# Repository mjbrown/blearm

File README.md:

# blearm
Open source hardware, firmware, and software for a Bluetooth Low Energy PiHAT.  This PiHAT was used to control a robot arm demonstration for Maker Faire MSP.

1. Firmware includes BGScript and XML files which define the embedded Bluetooth Low Energy device.  
2. Mechanical files include all 3d printed models used to construct the robot arm.  
3. Hardware files include schematics and layout eagle files for the circuit board.  
4. Software includes python scripts used in the development of the hardware.xml settings for PWM.
5. Android includes the modified Bluetooth LE Android application used to control the blearm.

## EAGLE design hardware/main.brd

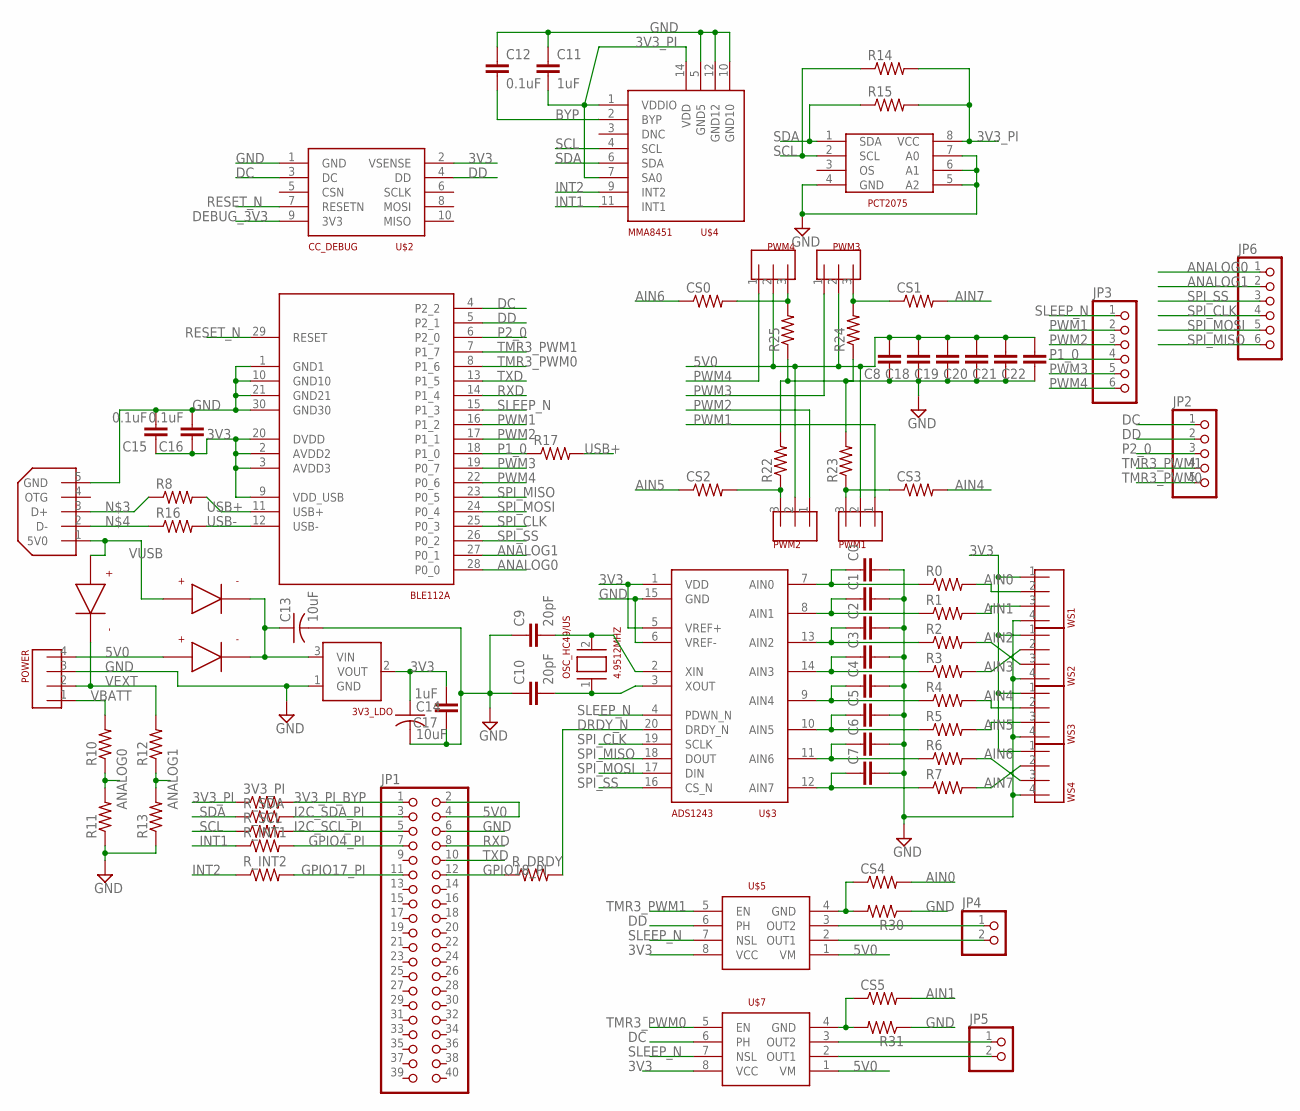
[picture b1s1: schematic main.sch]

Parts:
3V3_LDO: MCP1700; SOT23
3V3_PI: R-US_R0603; R0603
4.9512MHZ: OSC_HC49/US; HC49UP
BLE112A: BLE112A; BLE112
C0, C1, C2, C3, C4, C5, C6, C7, C8, C18, C19, C20, C21, C22: C-EUC0603; C0603
C9, C10: 20pF; C0603
C11, C17: 1uF; C0603
C12, C15, C16: 0.1uF; C0603
C13, C14: 10uF; C0805
CS0, CS1, CS2, CS3, CS4, CS5: R-US_R0603; R0603
JP1: PINHD-2X20; 2X20
JP2: PINHD-1X5; 1X05
JP3, JP6: PINHD-1X6; 1X06
JP4, JP5: PINHD-1X2; 1X02
PCT2075: PCT2075; SO-08
POWER: HDR_SPOX4
PWM1, PWM2, PWM3, PWM4: HDR_1X3
R0, R1, R2, R3, R4, R5, R6, R7, R8, R10, R11, R12, R13, R14, R15, R16, R17: R-US_R0603; R0603
R22, R23, R24, R25, R30, R31: R-US_R1206; R1206
R_DRDY: R-US_R0603; R0603
R_INT1, R_INT2: R-US_R0603; R0603
R_SCL: R-US_R0603; R0603
R_SDA: R-US_R0603; R0603
U$1, U$11, U$12: SCHOTTKEY_DIODE_1206; DIODE_1206
U$2: CC_DEBUG; HDR_2X5_127MM
U$3: ADS1243; TSSOP20
U$4: MMA8451; QFN16_3X3
U$5, U$7: DRV8838; WSON-8-PAD
U$6: MICRO_USB
WS1, WS2, WS3, WS4: HDR_1X4

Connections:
3V3: 3V3_LDO.2 (VOUT), BLE112A.2 (AVDD2), BLE112A.3 (AVDD3), BLE112A.9 (VDD_USB), BLE112A.20 (DVDD), C14.1, C15.1, C16.1, C17.2, U$2.2 (VSENSE), U$3.1 (VDD), U$3.5 (VREF+), U$5.8 (VCC), U$7.8 (VCC), WS1.1, WS2.1, WS3.1, WS4.1
3V3_PI: 3V3_PI.1, C11.2, PCT2075.8 (VCC), R14.2, R15.2, U$4.1 (VDDIO), U$4.7 (SA0), U$4.14 (VDD)
3V3_PI_BYP: 3V3_PI.2, JP1.1
5V0: C8.2, C18.2, C19.2, C20.2, C21.2, C22.2, JP1.2, JP1.4, POWER.4, PWM1.2, PWM2.2, PWM3.2, PWM4.2, U$5.1 (VM), U$7.1 (VM), U$12.CATHODE+
AIN0: CS4.2, R0.2, WS1.2
AIN1: CS5.2, R1.2, WS1.3
AIN2: R2.2, WS2.3
AIN3: R3.2, WS2.2
AIN4: CS3.2, R4.2, WS3.2
AIN5: CS2.1, R5.2, WS3.3
AIN6: CS0.1, R6.2, WS4.3
AIN7: CS1.2, R7.2, WS4.2
ANALOG0: BLE112A.28 (P0_0), JP6.1, R10.1, R11.2
ANALOG1: BLE112A.27 (P0_1), JP6.2, R12.1, R13.2
BYP: C12.2, U$4.2 (BYP)
DC: BLE112A.4 (P2_2), JP2.1, U$2.3 (DC), U$7.6 (PH)
DD: BLE112A.5 (P2_1), JP2.2, U$2.4 (DD), U$5.6 (PH)
DEBUG_3V3: U$2.9 (3V3)
DRDY_N: R_DRDY.2, U$3.20 (DRDY_N)
GND: 3V3_LDO.1 (GND), BLE112A.1 (GND1), BLE112A.10 (GND10), BLE112A.21 (GND21), BLE112A.30 (GND30), C0.2, C1.2, C2.2, C3.2, C4.2, C5.2, C6.2, C7.2, C8.1, C9.1, C10.1, C11.1, C12.1, C13.2, C14.2, C15.2, C16.2, C17.1, C18.1, C19.1, C20.1, C21.1, C22.1, JP1.6, PCT2075.4 (GND), PCT2075.5 (A2), PCT2075.6 (A1), PCT2075.7 (A0), POWER.3, R11.1, R13.1, R22.2, R23.2, R24.1, R25.1, R30.1, R31.1, U$2.1 (GND), U$3.6 (VREF-), U$3.15 (GND), U$4.5 (GND5), U$4.10 (GND10), U$4.12 (GND12), U$6.5 (GND), WS1.4, WS2.4, WS3.4, WS4.4
GPIO4_PI: JP1.7, R_INT1.2
GPIO17_PI: JP1.11, R_INT2.2
GPIO18_PI: JP1.12, R_DRDY.1
I2C_SCL_PI: JP1.5, R_SCL.2
I2C_SDA_PI: JP1.3, R_SDA.2
INT1: R_INT1.1, U$4.11 (INT1)
INT2: R_INT2.1, U$4.9 (INT2)
unnamed: C0.1, R0.1, U$3.7 (AIN0)
unnamed: C1.1, R1.1, U$3.8 (AIN1)
unnamed: R8.1, U$6.3 (D+)
unnamed: R16.1, U$6.2 (D-)
unnamed: 3V3_LDO.3 (VIN), C13.1, U$11.ANODE-, U$12.ANODE-
unnamed: C2.1, R2.1, U$3.13 (AIN2)
unnamed: C3.1, R3.1, U$3.14 (AIN3)
unnamed: C4.1, R4.1, U$3.9 (AIN4)
unnamed: C5.1, R5.1, U$3.10 (AIN5)
unnamed: C6.1, R6.1, U$3.11 (AIN6)
unnamed: C7.1, R7.1, U$3.12 (AIN7)
unnamed: JP4.1, U$5.3 (OUT2)
unnamed: CS2.2, PWM2.3, R22.1
unnamed: CS3.1, PWM1.3, R23.1
unnamed: CS0.2, PWM4.3, R25.2
unnamed: CS1.1, PWM3.3, R24.2
unnamed: JP4.2, U$5.2 (OUT1)
unnamed: JP5.1, U$7.3 (OUT2)
unnamed: JP5.2, U$7.2 (OUT1)
unnamed: 4.9512MHZ.2, C9.2, U$3.2 (XIN)
unnamed: 4.9512MHZ.1, C10.2, U$3.3 (XOUT)
unnamed: CS4.1, R30.2, U$5.4 (GND)
unnamed: CS5.1, R31.2, U$7.4 (GND)
P1_0: BLE112A.18 (P1_0), JP3.4, R17.1
P2_0: BLE112A.6 (P2_0), JP2.3
PWM1: BLE112A.16 (P1_2), JP3.2, PWM1.1
PWM2: BLE112A.17 (P1_1), JP3.3, PWM2.1
PWM3: BLE112A.19 (P0_7), JP3.5, PWM3.1
PWM4: BLE112A.22 (P0_6), JP3.6, PWM4.1
RESET_N: BLE112A.29 (RESET), U$2.7 (RESETN)
RXD: BLE112A.14 (P1_4), JP1.8
SCL: PCT2075.2 (SCL), R14.1, R_SCL.1, U$4.4 (SCL)
SDA: PCT2075.1 (SDA), R15.1, R_SDA.1, U$4.6 (SDA)
SLEEP_N: BLE112A.15 (P1_3), JP3.1, U$3.4 (PDWN_N), U$5.7 (NSL), U$7.7 (NSL)
SPI_CLK: BLE112A.25 (P0_3), JP6.4, U$3.19 (SCLK)
SPI_MISO: BLE112A.23 (P0_5), JP6.6, U$3.18 (DOUT)
SPI_MOSI: BLE112A.24 (P0_4), JP6.5, U$3.17 (DIN)
SPI_SS: BLE112A.26 (P0_2), JP6.3, U$3.16 (CS_N)
TMR3_PWM0: BLE112A.8 (P1_6), JP2.5, U$7.5 (EN)
TMR3_PWM1: BLE112A.7 (P1_7), JP2.4, U$5.5 (EN)
TXD: BLE112A.13 (P1_5), JP1.10
USB+: BLE112A.11 (USB+), R8.2, R17.2
USB-: BLE112A.12 (USB-), R16.2
VBATT: POWER.1, R10.2
VEXT: POWER.2, R12.2, U$1.ANODE-
VUSB: U$1.CATHODE+, U$6.1 (5V0), U$11.CATHODE+

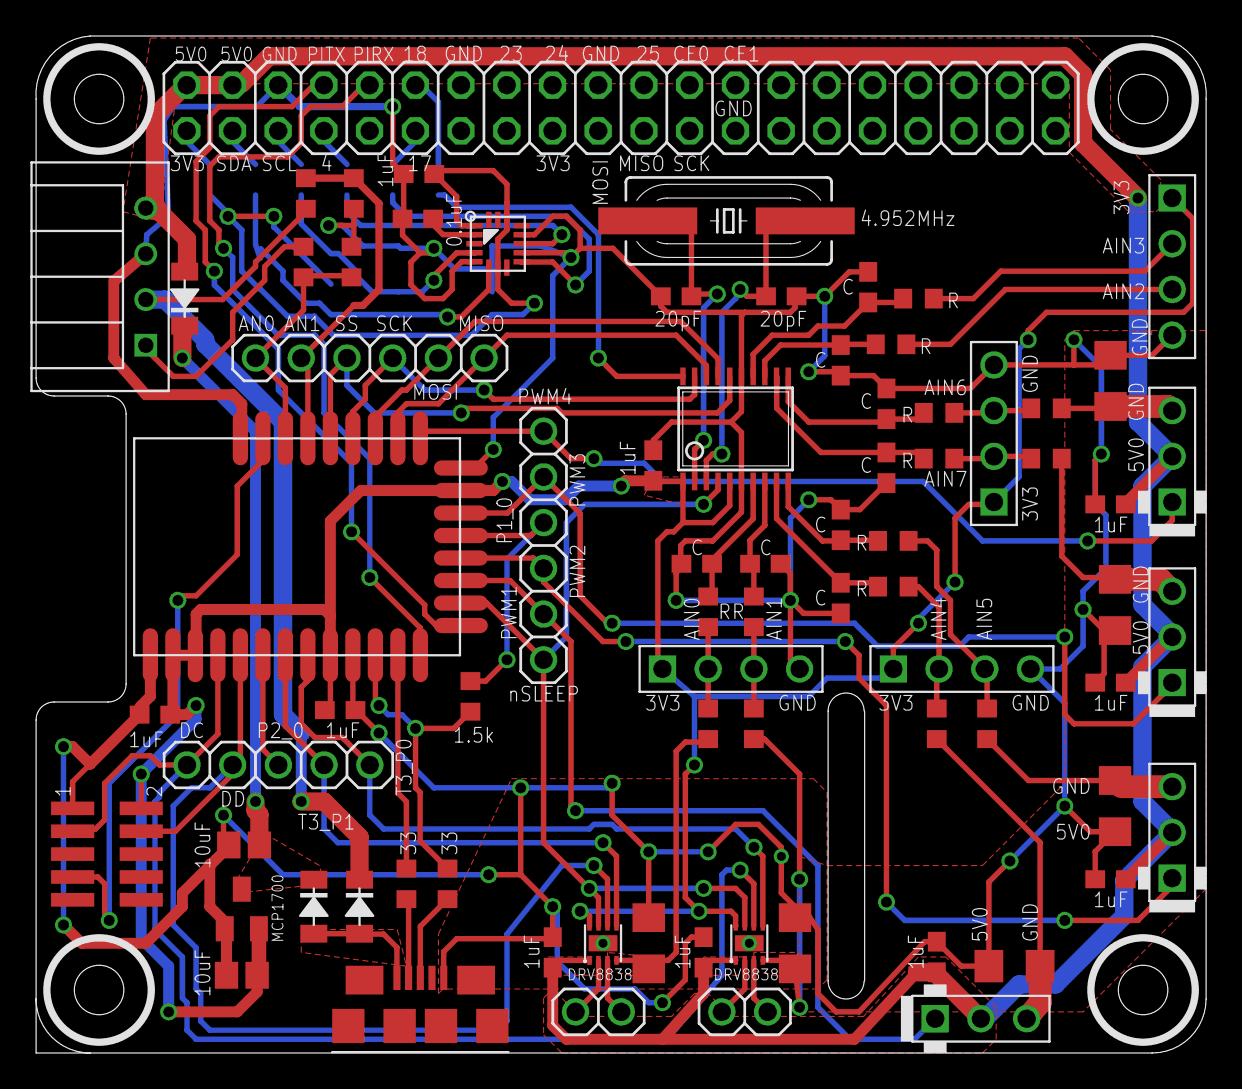
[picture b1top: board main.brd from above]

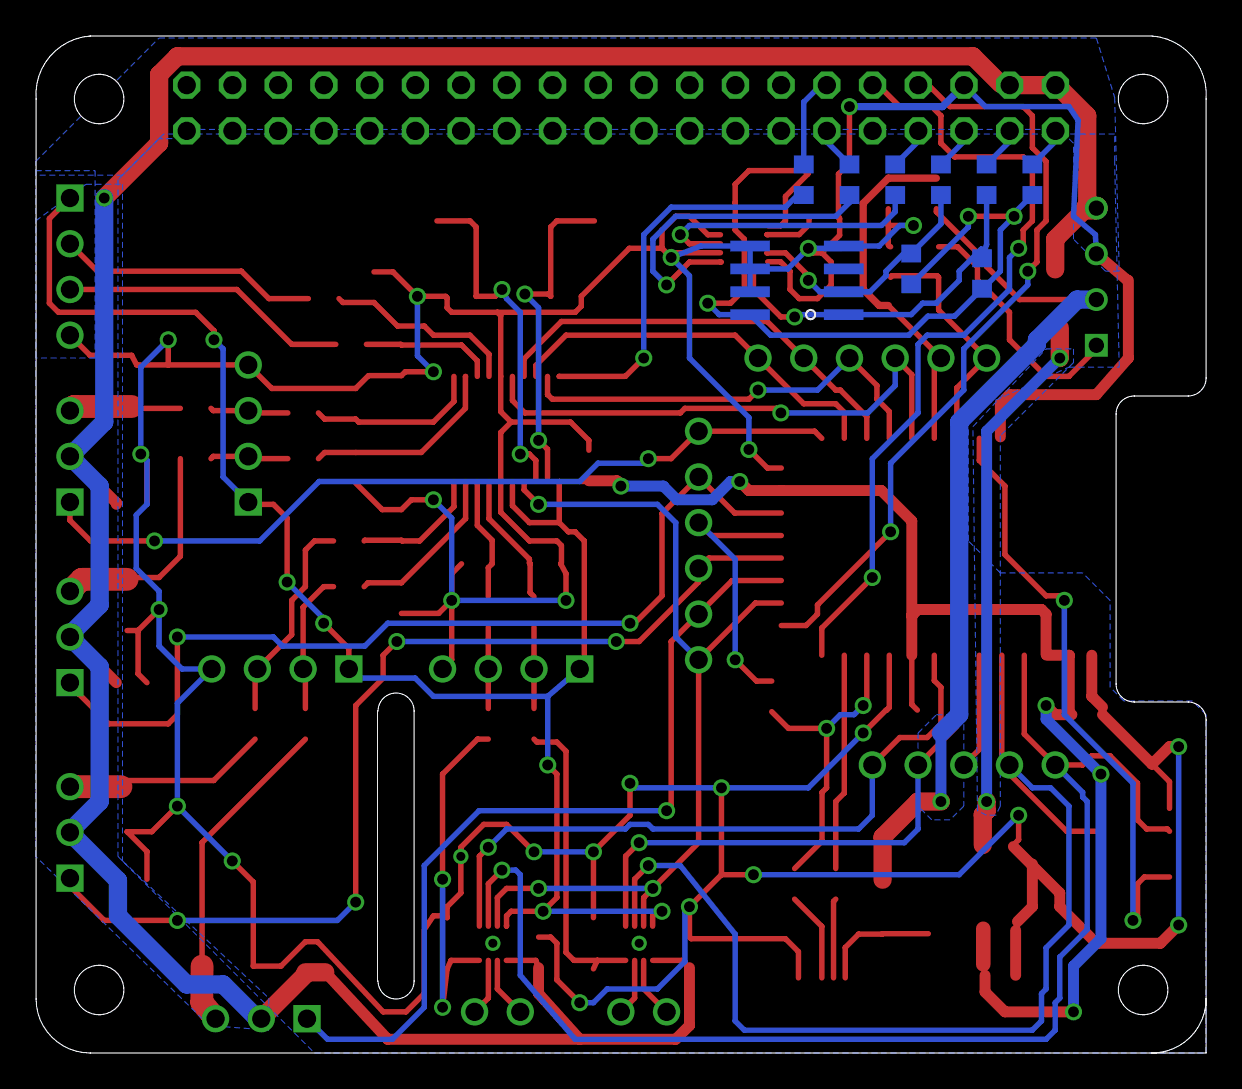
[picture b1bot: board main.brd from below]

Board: 2 copper layers, 65.0 x 56.5 mm, 86 parts (9 on the bottom side), 72 nets.

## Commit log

2015-03-20 Hardware and firmware for revision 1.
2015-03-20 Add temperature sensor read over I2C.
2015-04-13 Hardware revision 2, as ordered.
2015-05-29 Initial commit of unmodified Android BLE example.
2015-05-29 Initial commit of all models for 3d printing.
2015-05-29 BGScript for controlling all six PWMs via attribute writes.
2015-05-31 Android user interface for controlling robot arm shown at Maker Faire MSP.
2015-05-31 Update Readme.
